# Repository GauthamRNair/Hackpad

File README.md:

# Gautham's Macropad

### Inspiration

A personal macropad to easily navigate my notes when drawing with my Wacom.

### Specifications

BOM: 
- 4x Cherry MX Switches
- 4x SK6812 MINI Leds
- 1x XIAO RP2040
- 4x Blank DSA Keycaps
- 4x M3x16 Bolt
- 4x M3 Heatset
- 1x 0.91" 128x32 OLED Display

Schematic            |  PCB         |   Case
:-------------------------:|:-------------------------:|:-------------------------:|
  |    |

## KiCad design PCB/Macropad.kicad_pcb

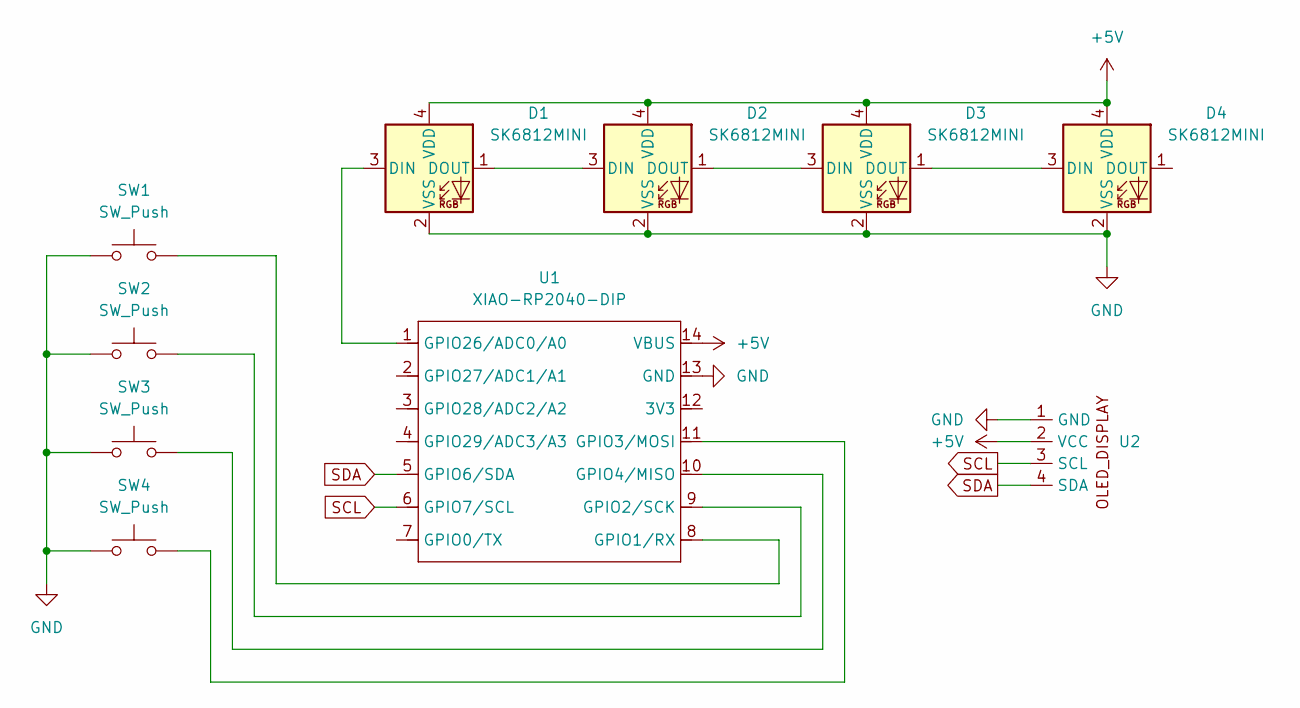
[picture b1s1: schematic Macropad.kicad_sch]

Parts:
D1, D2, D3, D4: SK6812MINI; LED_SK6812MINI_PLCC4_3.5x3.5mm_P1.75mm
SW1, SW2, SW3, SW4: SW_Push; SW_Cherry_MX_1.00u_PCB
U1: XIAO-RP2040-DIP
U2: SSD1306-0.91-OLED-4pin-128x32

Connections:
+5V: D1.4 (VDD), D2.4 (VDD), D3.4 (VDD), D4.4 (VDD), U1.14 (VBUS), U2.2 (VCC)
GND: D1.2 (VSS), D2.2 (VSS), D3.2 (VSS), D4.2 (VSS), SW1.1, SW2.1, SW3.1, SW4.1, U1.13 (GND), U2.1 (GND)
unnamed: D1.3 (DIN), U1.1 (GPIO26/ADC0/A0)
unnamed: D1.1 (DOUT), D2.3 (DIN)
unnamed: D2.1 (DOUT), D3.3 (DIN)
unnamed: D3.1 (DOUT), D4.3 (DIN)
unnamed: SW1.2, U1.8 (GPIO1/RX)
unnamed: SW2.2, U1.9 (GPIO2/SCK)
unnamed: SW4.2, U1.11 (GPIO3/MOSI)
unnamed: SW3.2, U1.10 (GPIO4/MISO)
SCL: U1.6 (GPIO7/SCL), U2.3 (SCL)
SDA: U1.5 (GPIO6/SDA), U2.4 (SDA)

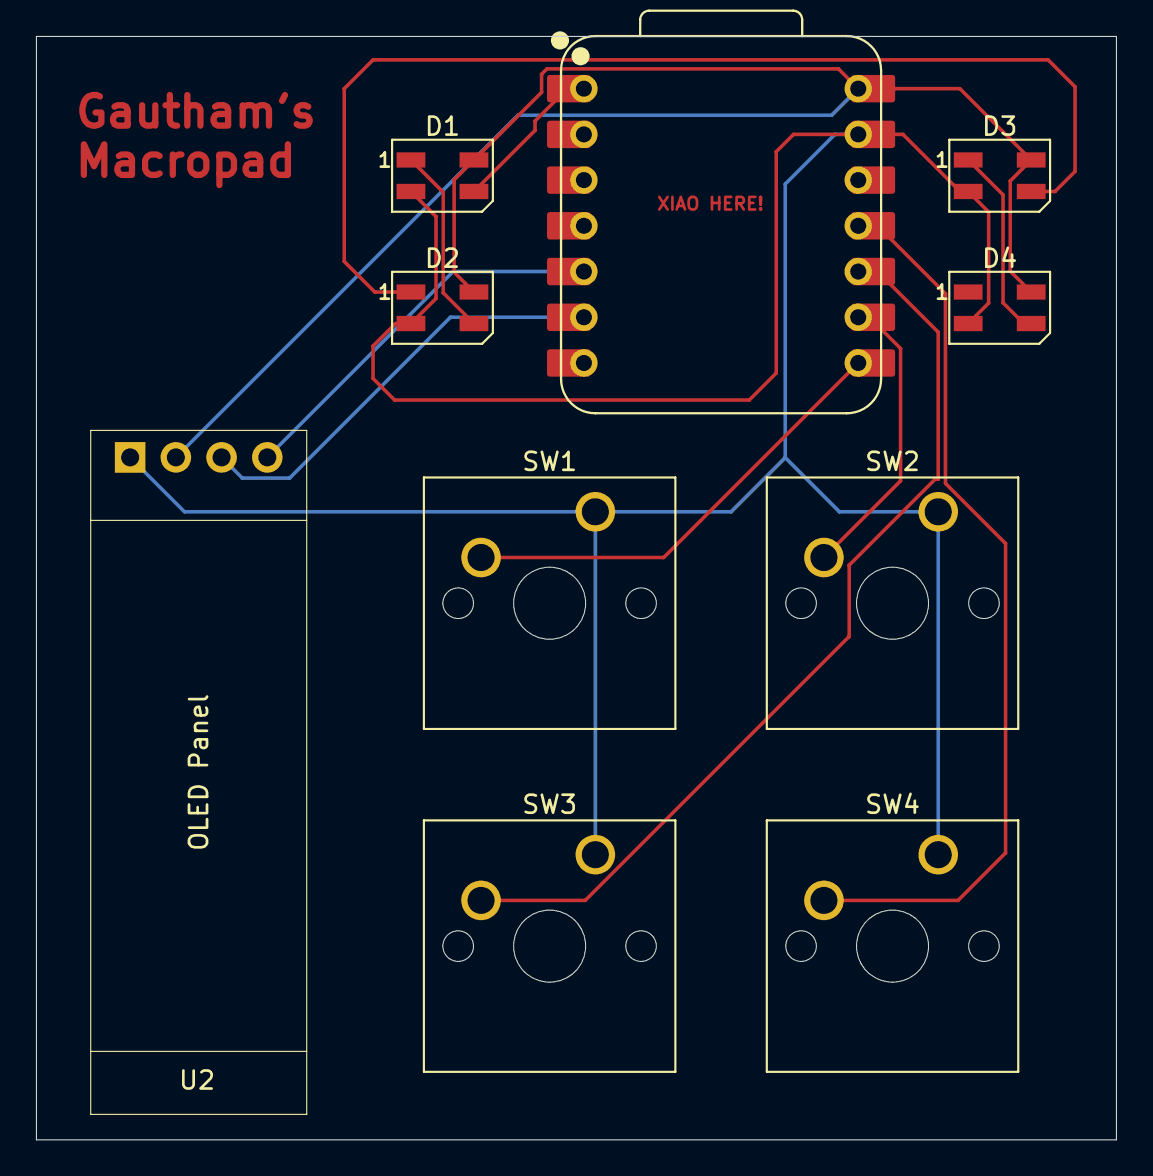
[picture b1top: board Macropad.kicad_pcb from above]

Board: 2 copper layers, 60.0 x 61.3 mm, 10 parts (0 on the bottom side), 12 nets.

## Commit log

2026-01-03 Added project files
2026-01-05 Added OLED
2026-01-05 modified code
2026-01-06 Added OLED to renders
2026-01-08 Fixed MacropadCase file
